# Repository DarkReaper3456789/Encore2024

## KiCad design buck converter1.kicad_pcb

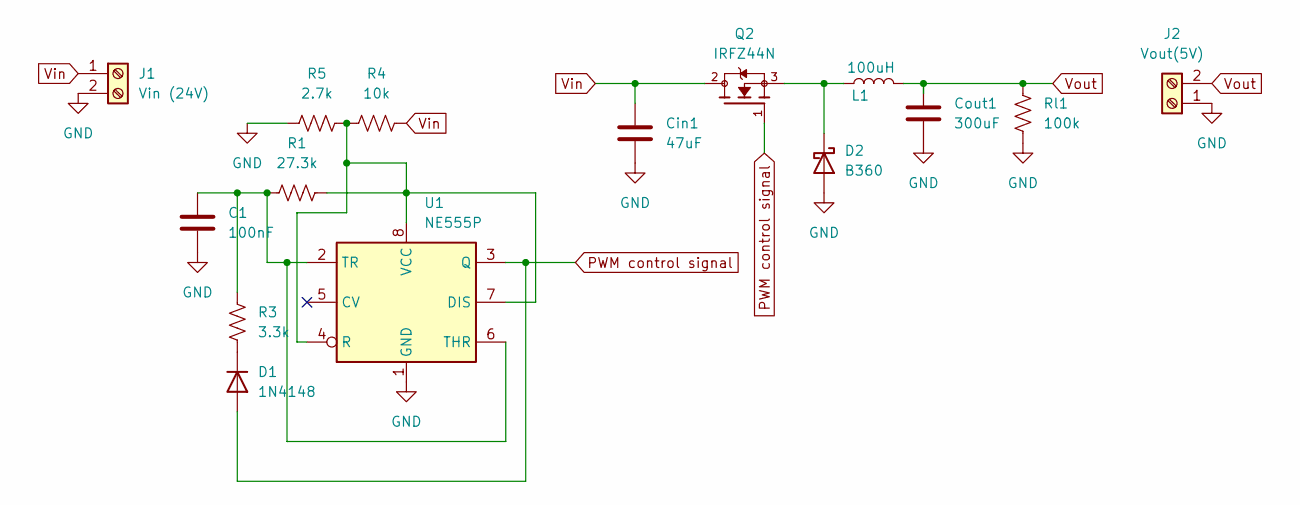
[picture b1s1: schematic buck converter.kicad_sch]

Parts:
C1: 100nF; C_0402_1005Metric_Pad0.74x0.62mm_HandSolder
Cin1: 47uF; C_Elec_3x5.4
Cout1: 300uF; C_1812_4532Metric
D1: 1N4148; D_DO-35_SOD27_P7.62mm_Horizontal
D2: B360; D_SMC
J1: Vin (24V); TerminalBlock_Phoenix_MKDS-1,5-2_1x02_P5.00mm_Horizontal
J2: Vout(5V); TerminalBlock_Phoenix_MKDS-1,5-2_1x02_P5.00mm_Horizontal
L1: 100uH; L_Vishay_IHLP-6767
Q2: IRFZ44N; TO254P1016X419X2286-3; PARTREV 09/21/10
R1: 27.3k; R_0603_1608Metric
R3: 3.3k; R_0402_1005Metric
R4: 10k; R_0603_1608Metric_Pad0.98x0.95mm_HandSolder
R5: 2.7k; R_0402_1005Metric
Rl1: 100k; R_1206_3216Metric_Pad1.30x1.75mm_HandSolder
U1: NE555P; DIP-8_W7.62mm

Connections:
GND: C1.2, Cin1.2, Cout1.2, D2.2 (A), J1.2, J2.1, R5.2, Rl1.2, U1.1 (GND)
unnamed: D1.1 (K), R3.2
unnamed: D2.1 (K), L1.1, Q2.3
unnamed: R1.1, R4.2, R5.1, U1.4 (R), U1.7 (DIS), U1.8 (VCC)
unnamed: C1.1, R1.2, R3.1, U1.2 (TR), U1.6 (THR)
PWM control signal: D1.2 (A), Q2.1, U1.3 (Q)
Vin: Cin1.1, J1.1, Q2.2, R4.1
Vout: Cout1.1, J2.2, L1.2, Rl1.1

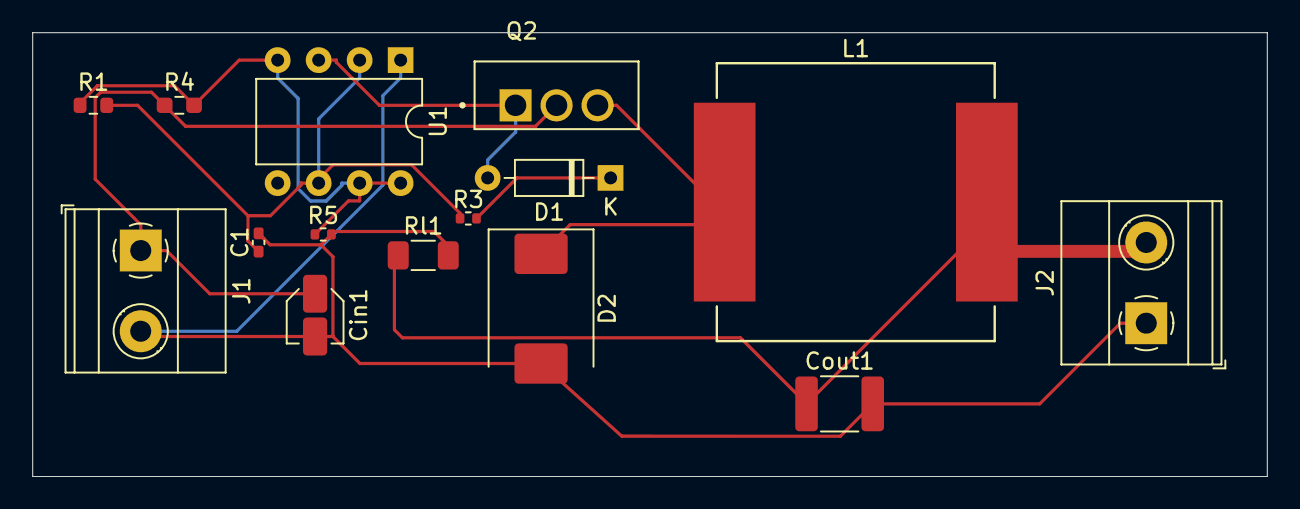
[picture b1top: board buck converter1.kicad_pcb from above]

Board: 2 copper layers, 76.5 x 27.5 mm, 15 parts (0 on the bottom side), 8 nets.

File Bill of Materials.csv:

"Source:","A:\DJCSE\Encore\buck converter\buck converter.kicad_sch"
"Date:","2024-09-27T02:16:39+0530"
"Tool:","Eeschema 8.0.5"
"Generator:","C:\Program Files\KiCad\8.0\bin\scripting\plugins/bom_csv_grouped_by_value.py"
"Component Count:","15"

"Collated Components:"

"Item","Qty","Reference(s)","Value","LibPart","Footprint","Datasheet","DNP","Availability","Check_prices","Datasheet","Description","Description_1","Footprint","MANUFACTURER","MAXIMUM_PACKAGE_HEIGHT","MF","MP","PARTREV","Package","Price","Purchase-URL","SNAPEDA_PN","STANDARD","Sim.Device","Sim.Pins","SnapEDA_Link"
"1","1","C1","100nF","Device:C","Capacitor_SMD:C_0402_1005Metric_Pad0.74x0.62mm_HandSolder","~","","","","~","Unpolarized capacitor","","Capacitor_SMD:C_0402_1005Metric_Pad0.74x0.62mm_HandSolder","","","","","","","","","","","","",""
"2","1","Cin1","47uF","Device:C","Capacitor_SMD:C_Elec_3x5.4","~","","","","~","Unpolarized capacitor","","Capacitor_SMD:C_Elec_3x5.4","","","","","","","","","","","","",""
"3","1","Cout1","300uF","Device:C","Capacitor_SMD:C_1812_4532Metric","~","","","","~","Unpolarized capacitor","","Capacitor_SMD:C_1812_4532Metric","","","","","","","","","","","","",""
"4","1","D1","1N4148","Diode:1N4148","Diode_THT:D_DO-35_SOD27_P7.62mm_Horizontal","https://assets.nexperia.com/documents/data-sheet/1N4148_1N4448.pdf","","","","https://assets.nexperia.com/documents/data-sheet/1N4148_1N4448.pdf","100V 0.15A standard switching diode, DO-35","","Diode_THT:D_DO-35_SOD27_P7.62mm_Horizontal","","","","","","","","","","","D","1=K 2=A",""
"5","1","D2","B360","Diode:B360","Diode_SMD:D_SMC","http://www.jameco.com/Jameco/Products/ProdDS/1538777.pdf","","","","http://www.jameco.com/Jameco/Products/ProdDS/1538777.pdf","60V 3A Schottky Barrier Rectifier Diode, SMC","","Diode_SMD:D_SMC","","","","","","","","","","","","",""
"6","1","J1","Vin (24V)","Connector:Screw_Terminal_01x02","TerminalBlock_Phoenix:TerminalBlock_Phoenix_MKDS-1,5-2_1x02_P5.00mm_Horizontal","~","","","","~","Generic screw terminal, single row, 01x02, script generated (kicad-library-utils/schlib/autogen/connector/)","","TerminalBlock_Phoenix:TerminalBlock_Phoenix_MKDS-1,5-2_1x02_P5.00mm_Horizontal","","","","","","","","","","","","",""
"7","1","J2","Vout(5V)","Connector:Screw_Terminal_01x02","TerminalBlock_Phoenix:TerminalBlock_Phoenix_MKDS-1,5-2_1x02_P5.00mm_Horizontal","~","","","","~","Generic screw terminal, single row, 01x02, script generated (kicad-library-utils/schlib/autogen/connector/)","","TerminalBlock_Phoenix:TerminalBlock_Phoenix_MKDS-1,5-2_1x02_P5.00mm_Horizontal","","","","","","","","","","","","",""
"8","1","L1","100uH","Device:L","Inductor_SMD:L_Vishay_IHLP-6767","~","","","","~","Inductor","","Inductor_SMD:L_Vishay_IHLP-6767","","","","","","","","","","","","",""
"9","1","Q2","IRFZ44N","IRFZ44N:IRFZ44N","New folder:TO254P1016X419X2286-3","","","In Stock","https://www.snapeda.com/parts/IRFZ44N/Infineon+Technologies/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","","","N-Channel 55 V 49A (Tc) 94W (Tc) Through Hole TO-220AB","New folder:TO254P1016X419X2286-3","Infineon","22.86 mm","Infineon Technologies","IRFZ44N","09/21/10","TO-220-3 Infineon","None","https://www.snapeda.com/api/url_track_click_mouser/?unipart_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 Technologies&part_name=IRFZ44N&search_term=None","IRFZ44N","IPC 7351B","","","https://www.snapeda.com/parts/IRFZ44N/Infineon+Technologies/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"
"10","1","R1","27.3k","Device:R_US","Resistor_SMD:R_0603_1608Metric","~","","","","~","Resistor, US symbol","","Resistor_SMD:R_0603_1608Metric","","","","","","","","","","","","",""
"11","1","R3","3.3k","Device:R_US","Resistor_SMD:R_0402_1005Metric","~","","","","~","Resistor, US symbol","","Resistor_SMD:R_0402_1005Metric","","","","","","","","","","","","",""
"12","1","R4","10k","Device:R_US","Resistor_SMD:R_0603_1608Metric_Pad0.98x0.95mm_HandSolder","~","","","","~","Resistor, US symbol","","Resistor_SMD:R_0603_1608Metric_Pad0.98x0.95mm_HandSolder","","","","","","","","","","","","",""
"13","1","R5","2.7k","Device:R_US","Resistor_SMD:R_0402_1005Metric","~","","","","~","Resistor, US symbol","","Resistor_SMD:R_0402_1005Metric","","","","","","","","","","","","",""
"14","1","Rl1","100k","Device:R_US","Resistor_SMD:R_1206_3216Metric_Pad1.30x1.75mm_HandSolder","~","","","","~","Resistor, US symbol","","Resistor_SMD:R_1206_3216Metric_Pad1.30x1.75mm_HandSolder","","","","","","","","","","","","",""
"15","1","U1","NE555P","Timer:NE555P","Package_DIP:DIP-8_W7.62mm","http://www.ti.com/lit/ds/symlink/ne555.pdf","","","","http://www.ti.com/lit/ds/symlink/ne555.pdf","Precision Timers, 555 compatible,  PDIP-8","","Package_DIP:DIP-8_W7.62mm","","","","","","","","","","","","",""

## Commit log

2024-09-26 Rename buck converter1.kicad_prl to buck converter.kicad_prl
2024-09-26 Rename buck converter1.kicad_pro to buck converter.kicad_pro
